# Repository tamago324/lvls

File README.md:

# レバーレスコントローラ

* choc v1

## LICENSE

<br />この 作品 は <a rel="license" href="http://creativecommons.org/licenses/by-nc/4.0/">クリエイティブ・コモンズ 表示 - 非営利 4.0 国際 ライセンス</a>の下に提供されています。

> 表示 — あなたは 適切なクレジットを表示し、ライセンスへのリンクを提供し、変更があったらその旨を示さなければなりません。これらは合理的であればどのような方法で行っても構いませんが、許諾者があなたやあなたの利用行為を支持していると示唆するような方法は除きます。
>
> 非営利 — あなたは営利目的でこの資料を利用してはなりません。

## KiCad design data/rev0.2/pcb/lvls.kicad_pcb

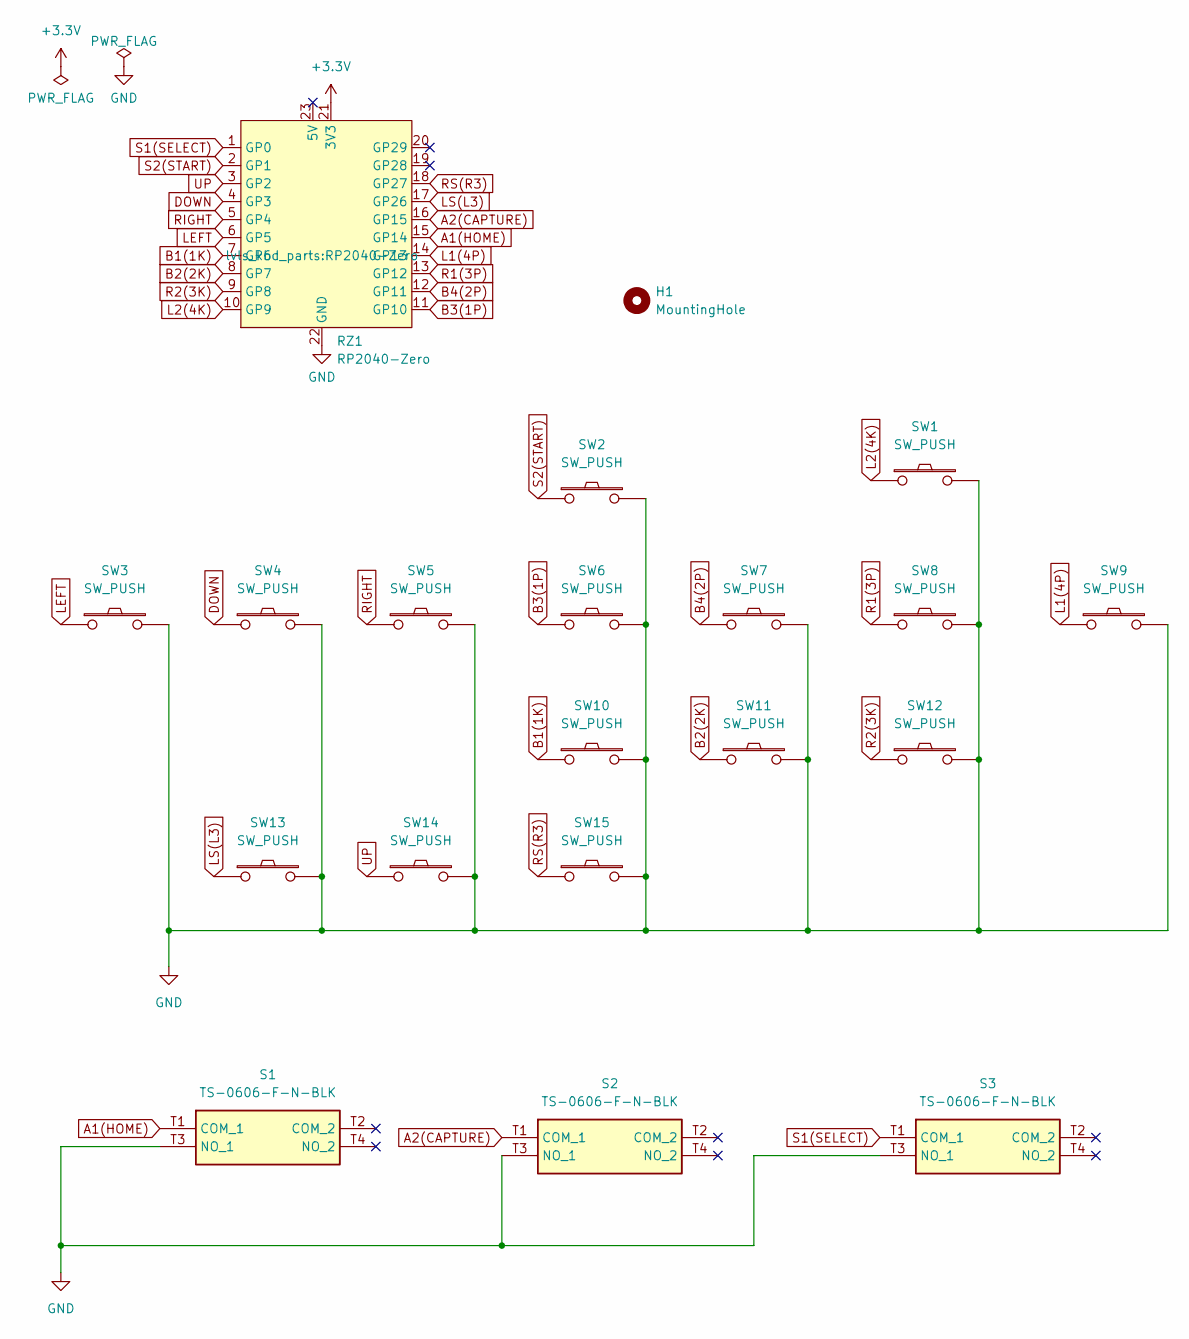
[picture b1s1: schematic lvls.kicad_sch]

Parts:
H1: MountingHole; nut_hole_12.6
RZ1: RP2040-Zero
S1, S2, S3: TS-0606-F-N-BLK; TS0606FNBLK; Manufacturer_Part_Number TS-0606-F-N-BLK
SW1, SW2, SW3, SW4, SW5, SW6, SW7, SW8, SW9, SW10, SW11, SW12, SW13, SW14, SW15: SW_PUSH; ChocV1_V2_Hotswap_mods

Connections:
+3.3V: RZ1.21 (3V3)
A1(HOME): RZ1.15 (GP14), S1.T1 (COM_1)
A2(CAPTURE): RZ1.16 (GP15), S2.T1 (COM_1)
B1(1K): RZ1.7 (GP6), SW10.1
B2(2K): RZ1.8 (GP7), SW11.1
B3(1P): RZ1.11 (GP10), SW6.1
B4(2P): RZ1.12 (GP11), SW7.1
DOWN: RZ1.4 (GP3), SW4.1
GND: RZ1.22 (GND), S1.T3 (NO_1), S2.T3 (NO_1), S3.T3 (NO_1), SW1.2, SW2.2, SW3.2, SW4.2, SW5.2, SW6.2, SW7.2, SW8.2, SW9.2, SW10.2, SW11.2, SW12.2, SW13.2, SW14.2, SW15.2
L1(4P): RZ1.14 (GP13), SW9.1
L2(4K): RZ1.10 (GP9), SW1.1
LEFT: RZ1.6 (GP5), SW3.1
LS(L3): RZ1.17 (GP26), SW13.1
R1(3P): RZ1.13 (GP12), SW8.1
R2(3K): RZ1.9 (GP8), SW12.1
RIGHT: RZ1.5 (GP4), SW5.1
RS(R3): RZ1.18 (GP27), SW15.1
S1(SELECT): RZ1.1 (GP0), S3.T1 (COM_1)
S2(START): RZ1.2 (GP1), SW2.1
UP: RZ1.3 (GP2), SW14.1

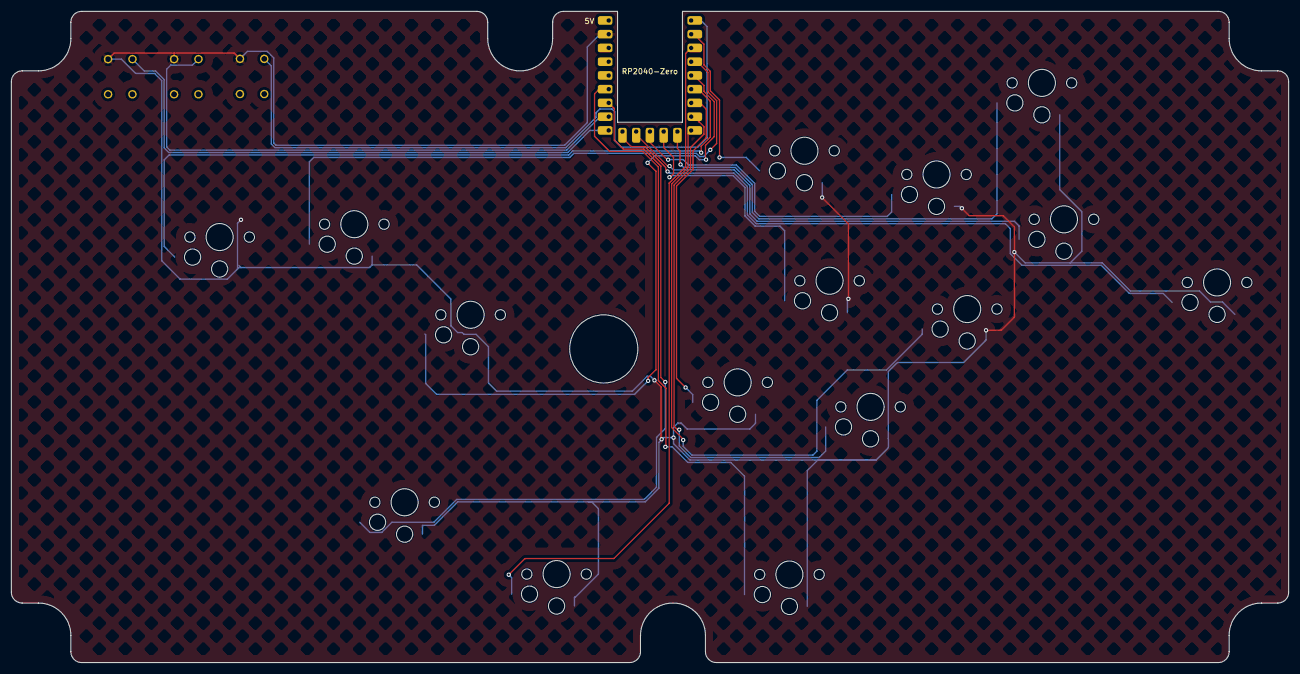
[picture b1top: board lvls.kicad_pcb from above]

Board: 2 copper layers, 236.1 x 120.4 mm, 20 parts (0 on the bottom side), 19 nets.

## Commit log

2023-10-11 init

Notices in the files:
README.md:
LICENSE:
CC BY-NC 4.0
